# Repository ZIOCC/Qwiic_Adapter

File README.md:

# Zio Qwiic Adapter

> This product can be available for purchase [here](https://www.smart-prototyping.com/Zio-Qwiic-Adapter.html).

#### Description

This useful little board will help you connect non-Qwiic-enabled boards with Qwiic-enabled modules.

Just solder your desired standard-pitch four-pin header to the board, and you’ve tapped into the Qwiic bus for breadboarding or connecting directly to modules without Qwiic connectors built in.

Two Qwiic connectors are set up for direct daisy-chaining with the attached module.

#### Specification

* Weight: 5g
* Dimension: 25.4x 8.6mm

#### Links

* [Eagle files](https://github.com/ZIOCC/Qwiic_Adapter)

> ###### About Zio
> Zio is a new line of open sourced, compact, and grid layout boards, fully integrated for Arduino and Qwiic ecosystem. Designed ideally for wearables, robotics, small-space limitations or other on the go projects. Check out other awesome Zio products [here](https://www.smart-prototyping.com/Zio).

> This board is a derivative of [Sparkfun's Qwiic Adapter](https://github.com/sparkfun/Qwiic_Adapter).

> All Zio products are released under the [Creative Commons Attribution, Share-Alike License](https://creativecommons.org/licenses/by-sa/4.0/), and in accordance with the principles of the [Open Source Hardware Association's OSHW Statement of Principles 1.0 and OSHW Definition 1.0.](https://www.oshwa.org/definition/)

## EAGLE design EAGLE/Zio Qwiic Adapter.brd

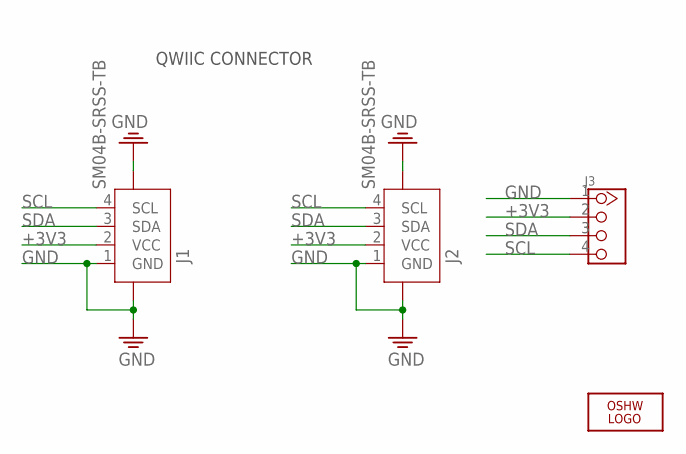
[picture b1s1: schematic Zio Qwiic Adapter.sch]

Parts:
J1, J2: SM04B-SRSS-TB; JST-SH-4P
J3: HEADER-4P-80/40MIL; 4P-2.54-80/40MIL
LOGO1: LOGO-OSHW-6MILX0070-NT; OSHW_6X70_NOTEXT

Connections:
+3V3: J1.2 (VCC), J2.2 (VCC), J3.2
GND: J1.1 (GND), J1.NC1 (5), J1.NC2 (6), J2.1 (GND), J2.NC1 (5), J2.NC2 (6), J3.1
SCL: J1.4 (SCL), J2.4 (SCL), J3.4
SDA: J1.3 (SDA), J2.3 (SDA), J3.3

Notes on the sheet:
QWIIC CONNECTOR

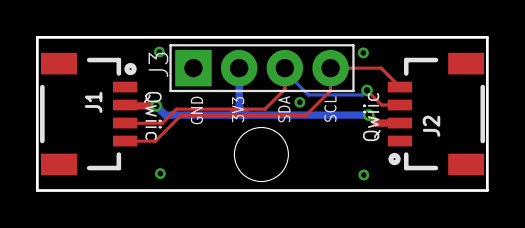
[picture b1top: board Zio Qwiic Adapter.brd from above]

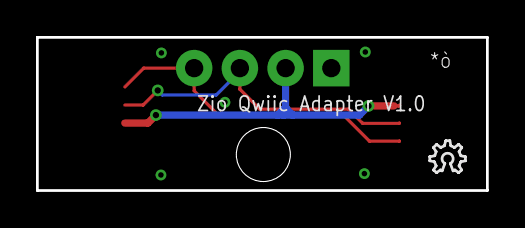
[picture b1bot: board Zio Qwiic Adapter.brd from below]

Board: 2 copper layers, 25.0 x 8.5 mm, 5 parts (2 on the bottom side), 4 nets.

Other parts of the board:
E$3: 6MM
